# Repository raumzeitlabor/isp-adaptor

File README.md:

This is a simple ISP adapter, which can be used to convert from 10-pin ISP to 6-pin ISP connectors and features a pin header for manual connections.

If you are etching the PCB yourself, you can either etch a double-side PCB or simply glue the transparent foil on the PCB to have pin indications.

Schematic and board are made in Eagle 6.1.0.

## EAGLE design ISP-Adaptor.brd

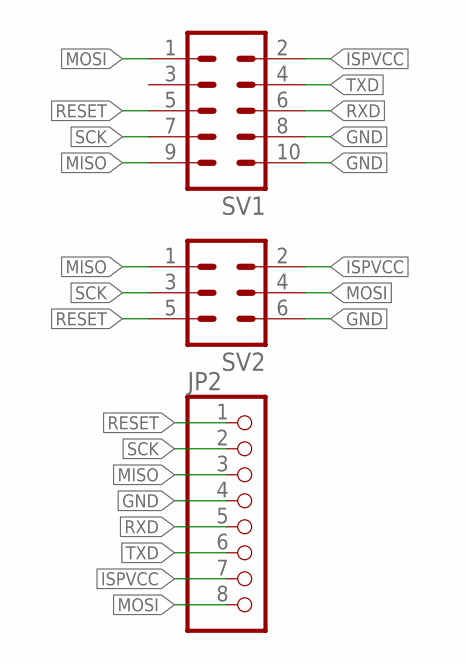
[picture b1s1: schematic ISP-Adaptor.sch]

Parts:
JP2: PINHD-1X8; 1X08
SV1: ML10
SV2: ML6

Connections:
GND: JP2.4, SV1.8, SV1.10, SV2.6
ISPVCC: JP2.7, SV1.2, SV2.2
MISO: JP2.3, SV1.9, SV2.1
MOSI: JP2.8, SV1.1, SV2.4
RESET: JP2.1, SV1.5, SV2.5
RXD: JP2.5, SV1.6
SCK: JP2.2, SV1.7, SV2.3
TXD: JP2.6, SV1.4

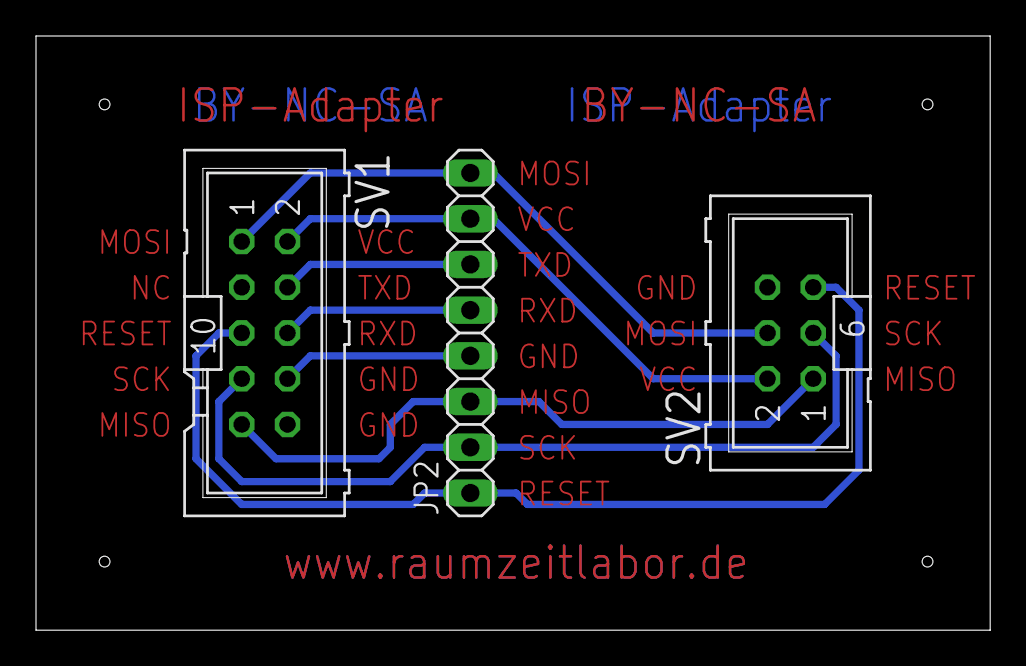
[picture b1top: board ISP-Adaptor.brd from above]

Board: 2 copper layers, 53.0 x 33.0 mm, 3 parts (0 on the bottom side), 8 nets.

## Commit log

2012-03-10 Added BOM
2012-03-10 Fixed mirroring in the PCB layout
2012-03-10 Fixed page layout to A4
2012-03-11 Removed useless files, removed filled pads
